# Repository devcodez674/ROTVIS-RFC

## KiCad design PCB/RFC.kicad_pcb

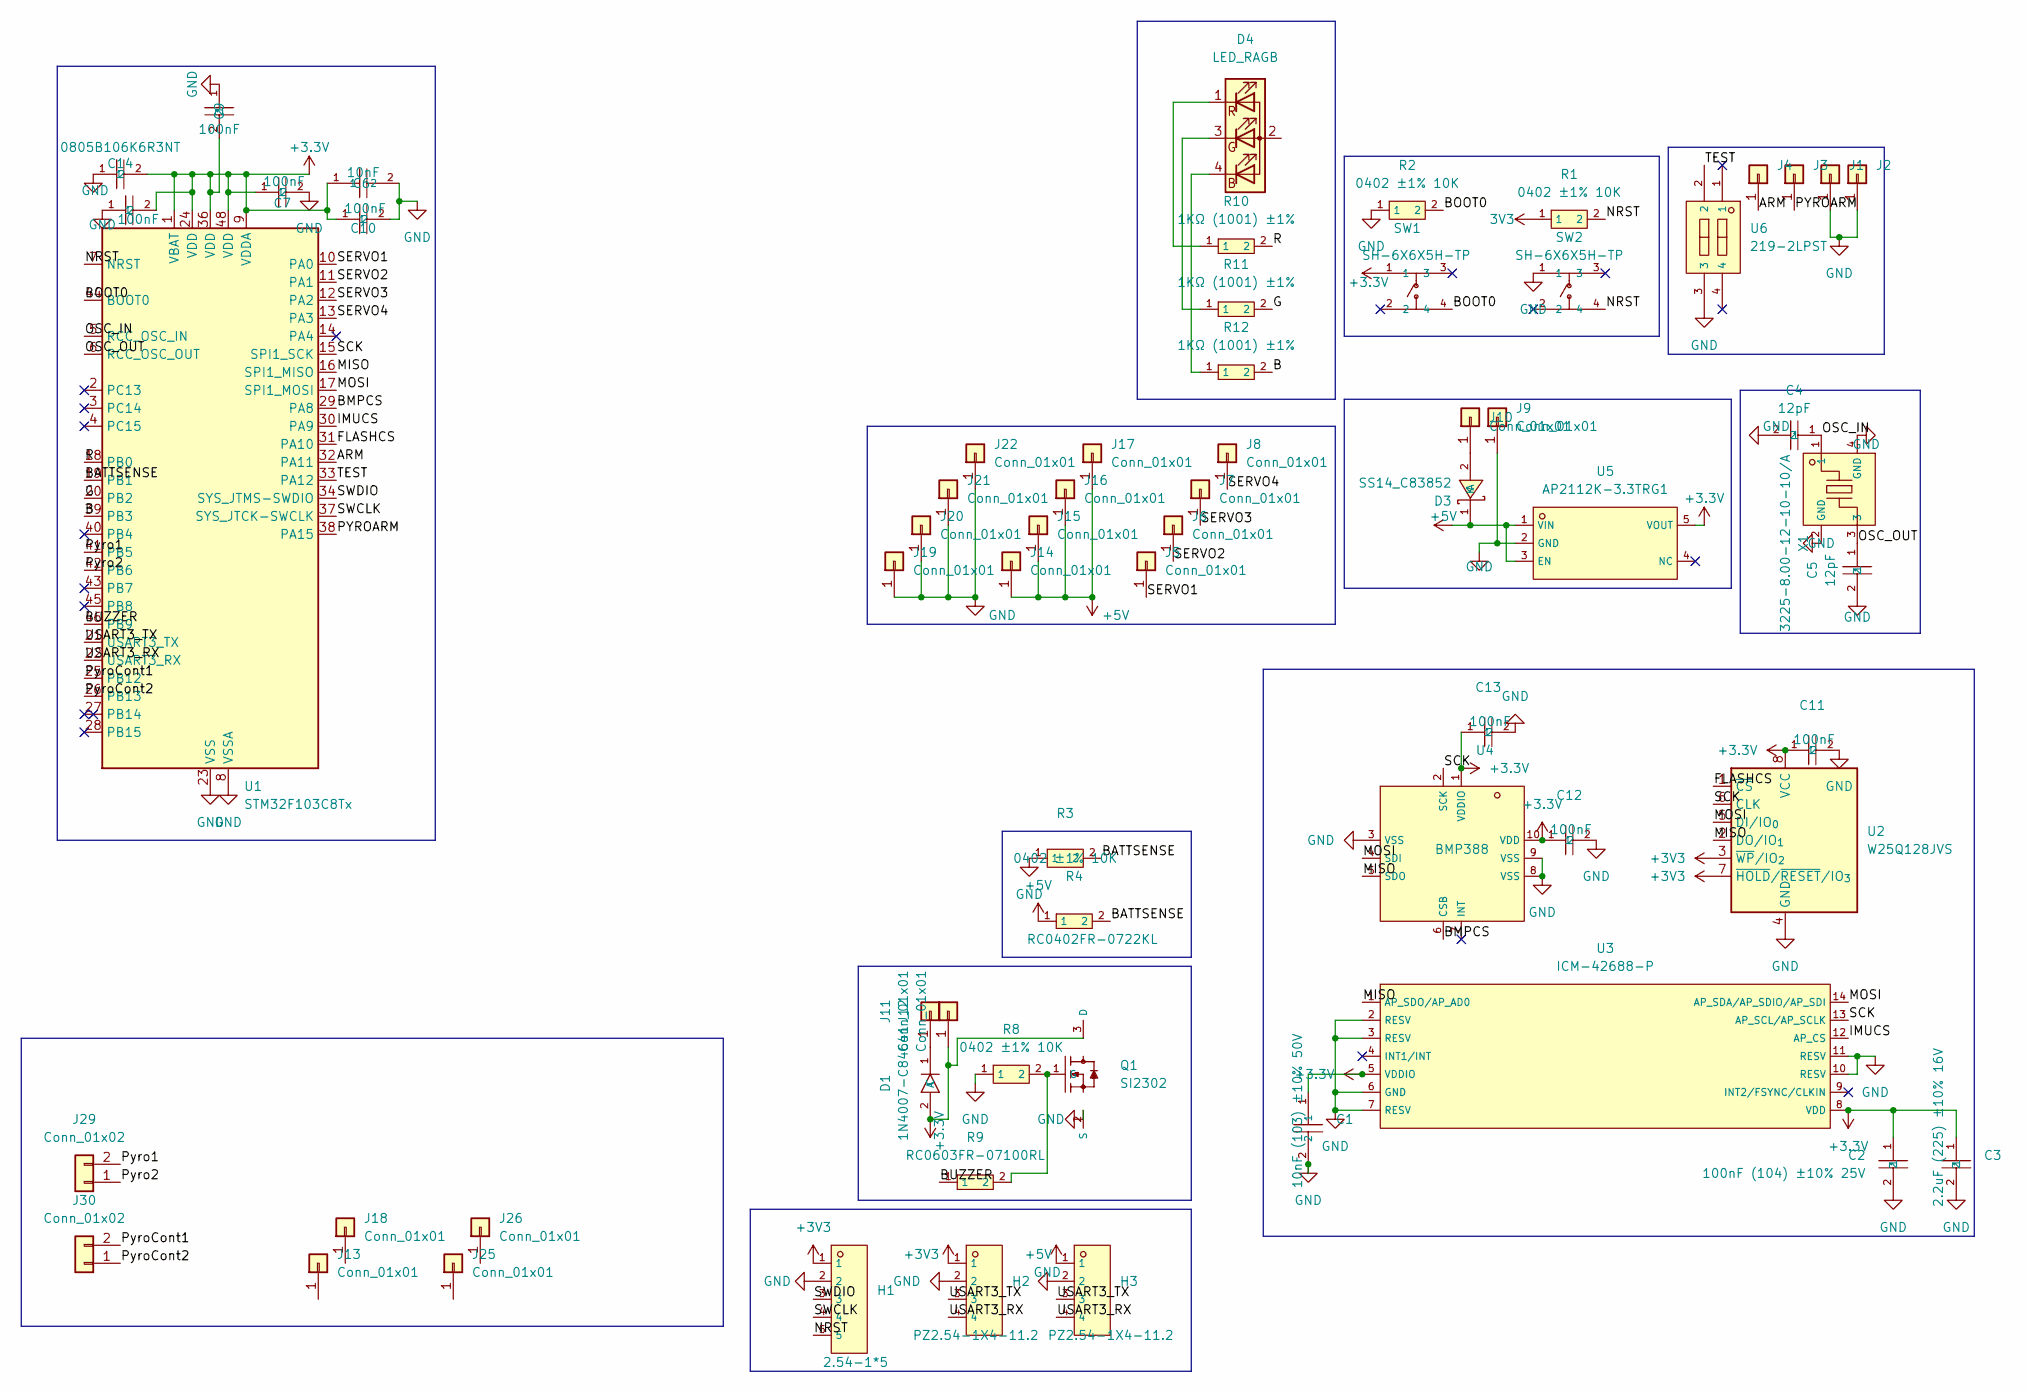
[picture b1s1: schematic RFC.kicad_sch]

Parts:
C1: 10nF (103) ±10% 50V; C57112_C0603; LCSC C57112
C2: 100nF (104) ±10% 25V; C1590_C0603; LCSC C1590
C3: 2.2uF (225) ±10% 16V; C23630_C0603; LCSC C23630
C4, C5: 12pF; C1642_C0603; LCSC C1642
C6: 10nF; C57112_C0603; LCSC C57112
C7, C8, C9, C10, C11, C12, C13: 100nF; C1590_C0603; LCSC C1590
C14: 0805B106K6R3NT; C105483_C0805; LCSC C105483
D1: 1N4007-C84641; C84641_DO-41_BD2_4-L4_7-P8_70-D0_9-RD; LCSC C84641
D3: SS14_C83852; C83852_SMA_L4_3-W2_6-LS5_2-RD; LCSC C83852
D4: LED_RAGB; LED_D5.0mm-4_RGB
H1: 2.54-1*5; C5156614_HDR-TH_5P-P2_54-V-M; LCSC C5156614
H2, H3: PZ2.54-1X4-11.2; C29779969_HDR-TH_4P-P2_54-V-M; LCSC C29779969
J1, J2, J3, J4, J5, J6, J7, J8, J11, J12, J13, J14, J15, J16, J17, J18, J19, J20, J21, J22, J25, J26: Conn_01x01; SolderWire-1sqmm_1x01_D1.4mm_OD2.7mm
J9, J10: Conn_01x01; SolderWire-1sqmm_1x01_D1.4mm_OD3.9mm
J29, J30: Conn_01x02
Q1: SI2302; C181087_SOT-23-3_L2_9-W1_3-P1_90-LS2_4-BR; LCSC C181087
R1, R2, R3, R8: 0402 ±1% 10K; C2889342_R0402; LCSC C2889342
R4: RC0402FR-0722KL; C82868_R0402; LCSC C82868
R9: RC0603FR-07100RL; C105588_R0603; LCSC C105588
R10, R11, R12: 1KΩ (1001) ±1%; C22548_R0603; LCSC C22548
SW1, SW2: SH-6X6X5H-TP; C42416254_SW-SMD_SH-6X6X4_5H-TP; LCSC C42416254
U1: STM32F103C8Tx; LQFP-48_7x7mm_P0.5mm
U2: W25Q128JVS; SOIC-8_5.3x5.3mm_P1.27mm
U3: ICM-42688-P; C1850418_LGA-14_L3_0-W2_5-P0_50-TL; LCSC C1850418
U4: BMP388; C779278_SENSORM-SMD_BMP388; LCSC C779278
U5: AP2112K-3.3TRG1; C51118_SOT-25-5_L2_9-W1_6-P0_95-LS2_8-BL; LCSC C51118
U6: 219-2LPST; C2842684_SW-SMD_CTS_219-2LPST; LCSC C2842684
X1: 3225-8.00-12-10-10/A; C518155_CRYSTAL-SMD_4P-L3_2-W2_5-BL; LCSC C518155

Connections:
3V3: R1.1
+3.3V: C1.1, C2.1, C3.1, C6.1, C7.1, C8.2, C9.2, C10.1, C11.1, C12.1, C13.1, C14.2, D1.2 (A), J12.1 (Pin_1_1), Q1.3 (D), SW1.1, U1.1 (VBAT), U1.9 (VDDA), U1.24 (VDD), U1.36 (VDD), U1.48 (VDD), U2.8 (VCC), U3.5 (VDDIO), U3.8 (VDD), U4.1 (VDDIO), U4.10 (VDD), U5.5 (VOUT)
+3V3: H1.1, H2.1, U2.3 (~WP/IO_{2}), U2.7 (~HOLD/~RESET/IO_{3})
+5V: D3.1 (K), H3.1, J14.1 (Pin_1_1), J15.1 (Pin_1_1), J16.1 (Pin_1_1), J17.1 (Pin_1_1), R4.1, U5.1 (VIN), U5.3 (EN)
/ARM: J4.1 (Pin_1_1), U1.32 (PA11)
/B: R12.2, U1.39 (PB3)
/BATTSENSE: R3.2, R4.2, U1.19 (PB1)
/BMPCS: U1.29 (PA8), U4.6 (CSB)
/BOOT0: R2.2, SW1.4, U1.44 (BOOT0)
/BUZZER: R9.1, U1.46 (PB9)
/FLASHCS: U1.31 (PA10), U2.1 (~CS)
/G: R11.2, U1.20 (PB2)
/IMUCS: U1.30 (PA9), U3.12 (AP_CS)
/MISO: U1.16 (SPI1_MISO), U2.2 (DO/IO_{1}), U3.1 (AP_SDO/AP_AD0), U4.5 (SDO)
/MOSI: U1.17 (SPI1_MOSI), U2.5 (DI/IO_{0}), U3.14 (AP_SDA/AP_SDIO/AP_SDI), U4.4 (SDI)
/NRST: H1.5, R1.2, SW2.4, U1.7 (NRST)
/OSC_IN: C4.1, U1.5 (RCC_OSC_IN), X1.1
/OSC_OUT: C5.1, U1.6 (RCC_OSC_OUT), X1.3
/PYROARM: J3.1 (Pin_1_1), U1.38 (PA15)
/Pyro1: J29.2, U1.41 (PB5)
/Pyro2: J29.1, U1.42 (PB6)
/PyroCont1: J30.2, U1.25 (PB12)
/PyroCont2: J30.1, U1.26 (PB13)
/R: R10.2, U1.18 (PB0)
/SCK: U1.15 (SPI1_SCK), U2.6 (CLK), U3.13 (AP_SCL/AP_SCLK), U4.2 (SCK)
/SERVO1: J5.1 (Pin_1_1), U1.10 (PA0)
/SERVO2: J6.1 (Pin_1_1), U1.11 (PA1)
/SERVO3: J7.1 (Pin_1_1), U1.12 (PA2)
/SERVO4: J8.1 (Pin_1_1), U1.13 (PA3)
/SWCLK: H1.4, U1.37 (SYS_JTCK-SWCLK)
/SWDIO: H1.3, U1.34 (SYS_JTMS-SWDIO)
/TEST: U1.33 (PA12), U6.2
/USART3_RX: H2.4, H3.4, U1.22 (USART3_RX)
/USART3_TX: H2.3, H3.3, U1.21 (USART3_TX)
GND: C1.2, C2.2, C3.2, C4.2, C5.2, C6.2, C7.2, C8.1, C9.1, C10.2, C11.2, C12.2, C13.2, C14.1, H1.2, H2.2, H3.2, J1.1 (Pin_1_1), J2.1 (Pin_1_1), J9.1 (Pin_1_1), J19.1 (Pin_1_1), J20.1 (Pin_1_1), J21.1 (Pin_1_1), J22.1 (Pin_1_1), Q1.2 (S), R2.1, R3.1, R8.1, SW2.1, U1.8 (VSSA), U1.23 (VSS), U1.35 (VSS), U1.47 (VSS), U2.4 (GND), U3.2 (RESV), U3.3 (RESV), U3.6 (GND), U3.7 (RESV), U3.10 (RESV), U3.11 (RESV), U4.3 (VSS), U4.8 (VSS), U4.9 (VSS), U5.2 (GND), U6.3, X1.2 (GND), X1.4 (GND)
unnamed: D1.1 (C), J11.1 (Pin_1_1)
unnamed: D3.2 (A), J10.1 (Pin_1_1)
unnamed: D4.4 (BK), R12.1
unnamed: D4.3 (GK), R11.1
unnamed: D4.1 (RK), R10.1
unnamed: Q1.1 (G), R8.2, R9.2

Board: 4 copper layers, 67 parts (0 on the bottom side), 36 nets, no tracks yet.

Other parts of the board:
J23, J24, J27, J28: Conn_01x01; SolderWire-1sqmm_1x01_D1.4mm_OD2.7mm

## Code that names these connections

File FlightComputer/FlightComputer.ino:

#include <SPI.h>
#include <ICM42688.h>
#include <SPIMemory.h>
#include <Adafruit_Sensor.h>
#include <Adafruit_BMP3XX.h>
#include <math.h>
#include <Servo.h>

#define PyroChnl1 PB5
#define PyroChnl2 PB6 
#define PyroChnl3 PB7 
#define PyroChnl4 PB8 

#define PyroCont1 PB12
#define PyroCont2 PB13
#define PyroCont3 PB14
#define PyroCont4 PB15

#define FinServo1 PA0
#define FinServo2 PA1
#define FinServo3 PA2
#define FinServo4 PA3           
#define armPin PA11
#define testPin PA12
#define baroCsPin PA8
#define imuCsPin PA9
#define flashCsPin PA10
#define BATT_PIN PA7
#define buzzerPin PB9
#define ledPin PB0


struct IMUData {
  float ax, ay, az, gx, gy, gz;
};
struct BaroData {
  float pressure, altitude, temperature;
};
struct EstimatedData {
  float pitch, roll, yaw;
  float altitude, BatteryVoltage, verticalVelocity;
};
struct FlightLog {
   uint32_t timestamp; 
    // barometer data
    float pressure, altitude, temperature;

    // IMU data
    float ax, ay, az, gx, gy, gz;

    // estimated data
    float pitch, roll, yaw;
    float estAltitude;
    float verticalVelocity;
    float batteryVoltage;


  //state data
  uint8_t logStateNo;
  uint8_t logPyroChnl;
  uint8_t logServoAngle[4];

};
enum flightState {
  stateIdle,
  stateCalibration,
  stateArmed,
  stateAscent,
  stateCoast,
  stateApogee,
  stateDescent,
  stateLanded,
  stateTest
};
//Struct objects
IMUData imuData;
BaroData baroData;
EstimatedData estimatedData;
flightState currentState = stateIdle;

//OBJECTs
Adafruit_BMP3XX BARO;
ICM42688 IMU(SPI, 11);
Servo servoFin1;
Servo servoFin2;
Servo servoFin3;
Servo servoFin4;
SPIFlash flash(flashCsPin, &SPI);

// Global state variables
  bool Test;
  float accelMagnitude;
  //Time
    unsigned long startTime;
    unsigned long endTime;
    unsigned long launchStart = 0;
    unsigned long apogeeStart = 0;
    unsigned long now = 0;
    unsigned long lastIMURead = 0;
    unsigned long lastBaroRead = 0;
    unsigned long lastLogTime = 0;
    unsigned long prevMicros = 0;
    uint8_t apogeeCounter = 0;
    uint8_t coastCounter = 0;
    unsigned long landingCounter = 0;
    unsigned long parachuteCounter = 0;
    float dt;
    //Baro
    float SeaLevelPressure_HPA = 1023.25;
    float previousAltitude = 0.0f;
  //Pyro
    int CurrPyroChnl = 0;
    bool pyroArmed = false;
  //Constants
    const float alpha = 0.98f;
    const float RADtoDEG = 57.2957795f;
  //battery
    const float BATT_DIV_RATIO = 4.0f;
    uint16_t battADC = 0;
    //target
    float targetPitch = 0;
    float targetYaw = 0;
    //control
    float Kp = 1;
    float Kd = 1;
    float pitchCmd = 0;
    float yawCmd = 0;
    float pitchError = 0;
    float yawError = 0;
  //Arrays
    bool pyroChnlState[5] = {false, false, false, false, false};
    uint8_t servoAngle[4];

void setup() {
  initialize();
}

void loop() {

  checkPyroState();
  Test = digitalRead(testPin);

  if (digitalRead(armPin) && (currentState == stateCalibration || currentState == stateTest)) {
    Serial.println("ARMED");
    currentState = stateArmed;
  } 

  timeStart();
  stateSwitcher();
  runDetectors();
}
